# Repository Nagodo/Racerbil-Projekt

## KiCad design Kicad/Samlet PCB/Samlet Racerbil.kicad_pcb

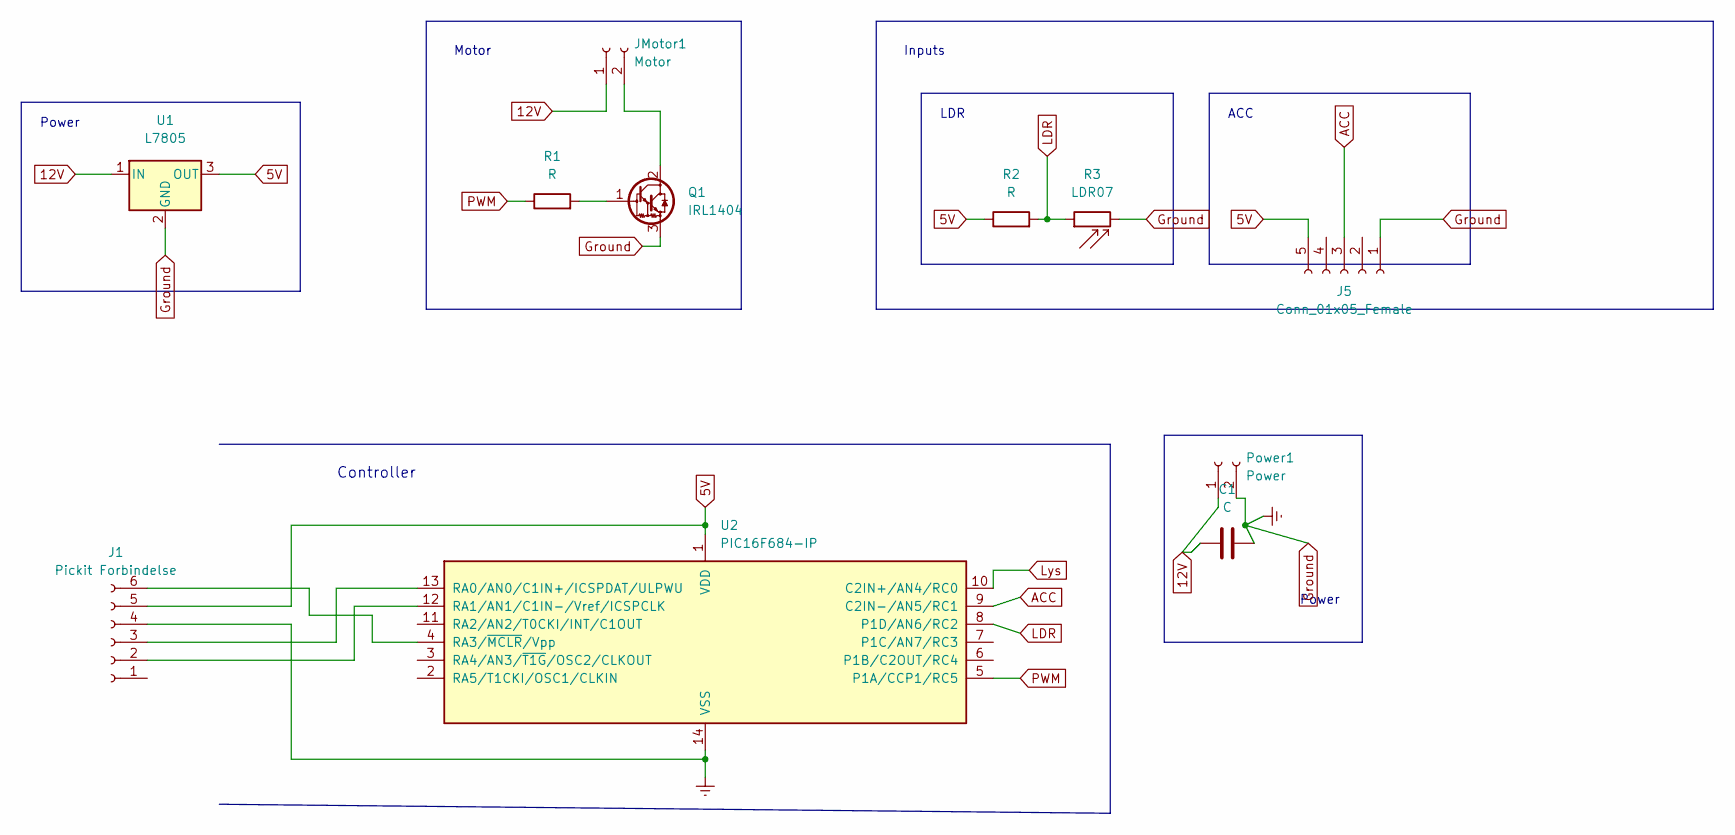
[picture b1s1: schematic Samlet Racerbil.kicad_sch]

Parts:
C1: C; CP_Radial_D7.5mm_P2.50mm
J1: Pickit Forbindelse; PinHeader_1x06_P2.54mm_Vertical
J5: Conn_01x05_Female; PinHeader_1x05_P2.54mm_Vertical
JMotor1: Motor; PinHeader_1x02_P2.54mm_Vertical
Power1: Power; PinHeader_1x02_P2.54mm_Vertical
Q1: IRL1404; TO-220-3_Vertical
R1, R2: R; R_Axial_DIN0207_L6.3mm_D2.5mm_P10.16mm_Horizontal
R3: LDR07; R_LDR_5.1x4.3mm_P3.4mm_Vertical
U1: L7805; TO-220-3_Vertical
U2: PIC16F684-IP; DIP-14_W7.62mm

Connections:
5V: J1.5, J5.5, R2.1, U1.3 (OUT), U2.1 (VDD)
12V: C1.1, JMotor1.1, Power1.1, U1.1 (IN)
ACC: J5.3, U2.9 (C2IN-/AN5/RC1)
Ground: C1.2, J1.4, J5.1, Power1.2, Q1.3 (E), R3.2, U1.2 (GND), U2.14 (VSS)
LDR: R2.2, R3.1, U2.8 (P1D/AN6/RC2)
Lys: U2.10 (C2IN+/AN4/RC0)
unnamed: J1.2, U2.12 (RA1/AN1/C1IN-/Vref/ICSPCLK)
unnamed: J1.3, U2.13 (RA0/AN0/C1IN+/ICSPDAT/ULPWU)
unnamed: J1.6, U2.4 (RA3/~MCLR/Vpp)
unnamed: JMotor1.2, Q1.2 (C)
unnamed: Q1.1 (B), R1.2
PWM: R1.1, U2.5 (P1A/CCP1/RC5)

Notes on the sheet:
Power
LDR
Motor
Inputs
ACC
Controller

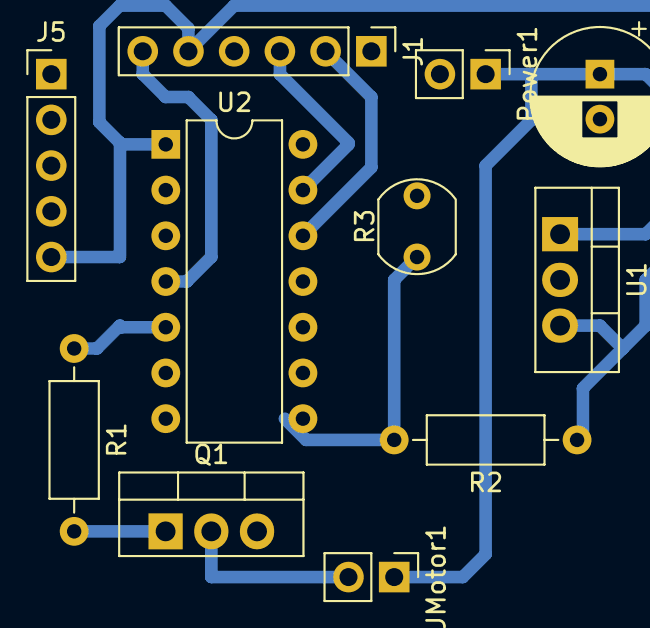
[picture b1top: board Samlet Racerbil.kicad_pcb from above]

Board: 2 copper layers, 11 parts (0 on the bottom side), 11 nets.

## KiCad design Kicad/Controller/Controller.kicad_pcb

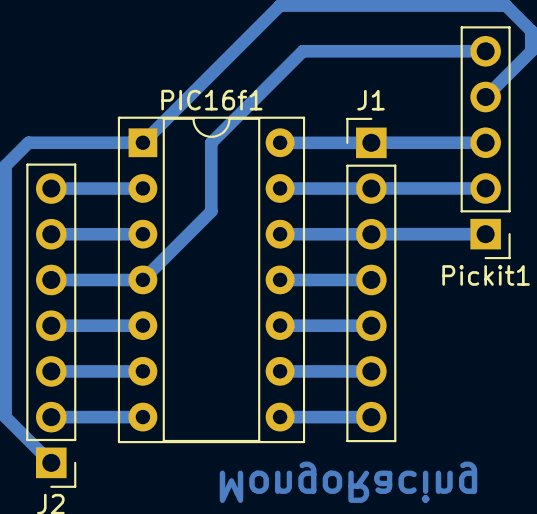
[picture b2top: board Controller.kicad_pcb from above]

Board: 2 copper layers, 4 parts (0 on the bottom side), 14 nets.

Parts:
J1, J2: Conn_01x07_Female; PinHeader_1x07_P2.54mm_Vertical
PIC16f1: PIC16F684-IP; DIP-14_W7.62mm_Socket
Pickit1: Conn_01x05_Female; PinHeader_1x05_P2.54mm_Vertical

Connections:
Earth: J1.1, PIC16f1.14 (VSS), Pickit1.3
unnamed: J1.2, PIC16f1.13 (RA0/AN0/C1IN+/ICSPDAT/ULPWU), Pickit1.2
unnamed: J1.3, PIC16f1.12 (RA1/AN1/C1IN-/Vref/ICSPCLK), Pickit1.1
unnamed: J1.4, PIC16f1.11 (RA2/AN2/T0CKI/INT/C1OUT)
unnamed: J1.5, PIC16f1.10 (C2IN+/AN4/RC0)
unnamed: J1.6, PIC16f1.9 (C2IN-/AN5/RC1)
unnamed: J1.7, PIC16f1.8 (P1D/AN6/RC2)
unnamed: J2.1, PIC16f1.1 (VDD), Pickit1.4
unnamed: J2.2, PIC16f1.7 (P1C/AN7/RC3)
unnamed: J2.3, PIC16f1.6 (P1B/C2OUT/RC4)
unnamed: J2.4, PIC16f1.5 (P1A/CCP1/RC5)
unnamed: J2.5, PIC16f1.4 (RA3/~MCLR/Vpp), Pickit1.5
unnamed: J2.6, PIC16f1.3 (RA4/AN3/~T1G/OSC2/CLKOUT)
unnamed: J2.7, PIC16f1.2 (RA5/T1CKI/OSC1/CLKIN)

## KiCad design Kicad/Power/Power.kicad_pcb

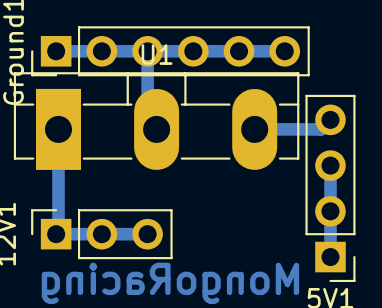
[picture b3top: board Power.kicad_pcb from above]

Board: 2 copper layers, 4 parts (0 on the bottom side), 3 nets.

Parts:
5V1: Conn_01x04_Female; PinHeader_1x04_P2.54mm_Vertical
12V1: Conn_01x03_Female; PinSocket_1x03_P2.54mm_Vertical
Ground1: Conn_01x06_Female; PinHeader_1x06_P2.54mm_Vertical
U1: L7805; TO-3P-3_Vertical

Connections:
Earth: Ground1.1, Ground1.2, Ground1.3, Ground1.4, Ground1.5, Ground1.6, U1.2 (GND)
unnamed: 5V1.1, 5V1.2, 5V1.3, 5V1.4, U1.3 (OUT)
unnamed: 12V1.1, 12V1.2, 12V1.3, U1.1 (IN)

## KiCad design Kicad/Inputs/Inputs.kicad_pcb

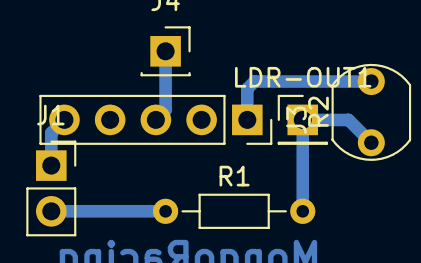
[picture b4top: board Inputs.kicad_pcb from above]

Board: 2 copper layers, 6 parts (0 on the bottom side), 5 nets.

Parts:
J1: 5V; PinSocket_1x02_P2.54mm_Vertical
J3: Conn_01x05_Female; PinSocket_1x05_P2.54mm_Vertical
J4: ACC OUT; PinSocket_1x01_P2.54mm_Vertical
LDR-OUT1: LDR-OUT; PinHeader_1x01_P2.54mm_Vertical
R1: 1000; R_Axial_DIN0204_L3.6mm_D1.6mm_P7.62mm_Horizontal
R2: LDR07; R_LDR_5.1x4.3mm_P3.4mm_Vertical

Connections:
Earth: J3.1, R2.2
unnamed: J1.1, J3.5
unnamed: J1.2, R1.1
unnamed: J3.3, J4.1
unnamed: LDR-OUT1.1, R1.2, R2.1

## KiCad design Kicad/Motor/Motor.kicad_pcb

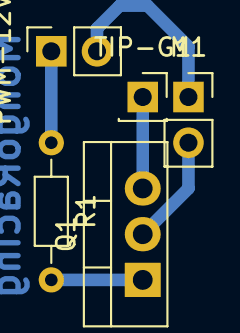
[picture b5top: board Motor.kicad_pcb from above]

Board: 2 copper layers, 5 parts (0 on the bottom side), 5 nets.

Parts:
M1: M 12V og M Gorund; PinSocket_1x02_P2.54mm_Vertical
PWM-12V1: PWM og 12V; PinSocket_1x02_P2.54mm_Vertical
Q1: TIP120; TO-220-3_Vertical
R1: R; R_Axial_DIN0204_L3.6mm_D1.6mm_P7.62mm_Horizontal
TIP-G1: Ground; PinSocket_1x01_P2.54mm_Vertical

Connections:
Earth: Q1.3 (E), TIP-G1.1
unnamed: M1.1, PWM-12V1.2
unnamed: M1.2, Q1.2 (C)
unnamed: PWM-12V1.1, R1.1
unnamed: Q1.1 (B), R1.2

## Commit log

2022-11-16 Kicad
2022-11-16 Samlet
2022-11-25 Text
2022-12-05 Capacitor
